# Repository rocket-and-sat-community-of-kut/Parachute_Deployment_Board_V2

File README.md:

# Parachute_Deployment_Board_V2

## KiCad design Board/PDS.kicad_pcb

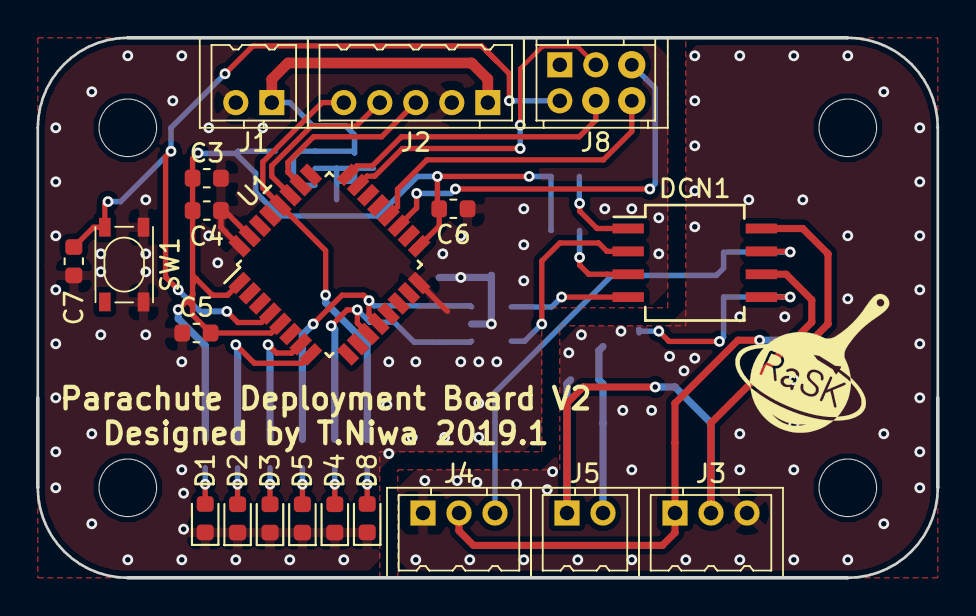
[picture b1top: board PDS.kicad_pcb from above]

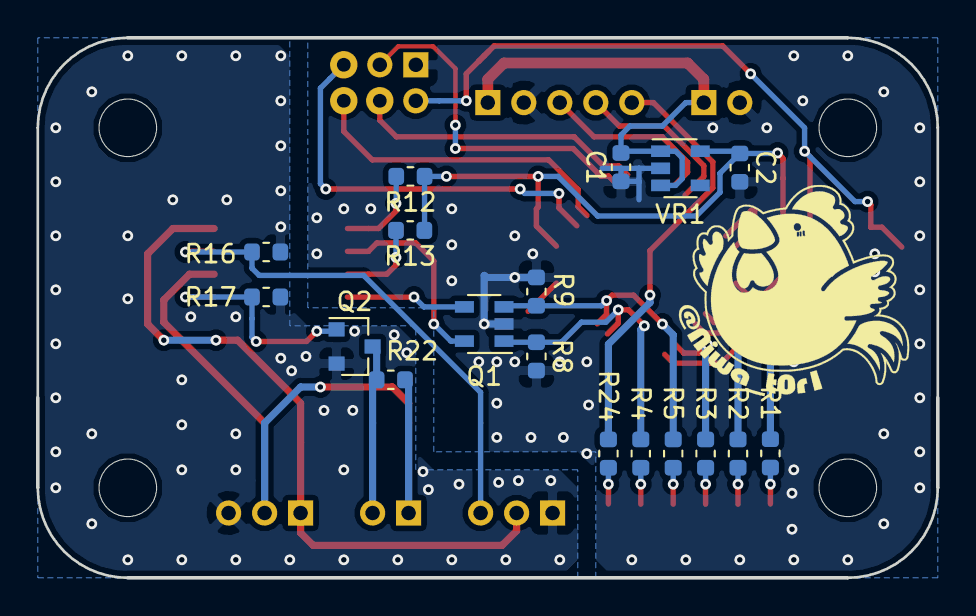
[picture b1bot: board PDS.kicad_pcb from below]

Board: 2 copper layers, 50.0 x 30.0 mm, 38 parts (18 on the bottom side), 31 nets.

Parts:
C1: 0.47u; C_0603_1608Metric
C2, C3: 4.7u; C_0603_1608Metric
C4, C6, C7: 0.1u; C_0603_1608Metric
C5: 0.01u; C_0603_1608Metric
D1, D2, D3, D8: LED; LED_0603_1608Metric
D4, D5: RED; LED_0603_1608Metric
DCN1: ACPL-227; SO-8_5.3x6.2mm_P1.27mm
J1: PWR; DF3A-2P-2DSA
J2: Port; DF3A-5P-2DSA
J3: Actuator_Port; DF3A-3P-2DSA
J4: Servo1; DF3A-3P-2DSA
J5: Air1; DF3A-2P-2DSA
J8: STLink+; DF11-6DP-2DSA2
Q1: DUAL; SOT-23-5
Q2: Q_NMOS_GSD; SOT-23
R1, R2, R3, R4, R5, R8, R9, R12, R13, R16, R17, R22, R24: 1k; R_0603_1608Metric
SW1: SW_Push_Dual; SW_SPST_SKRPACE010
U1: STM32F042K6Tx; LQFP-32_7x7mm_P0.8mm
VR1: NJM12888; SOT-23-5

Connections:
+3V3: C2.1, C3.2, C4.2, C5.2, C6.2, R1.1, R12.1, R13.1, U1.1, U1.5, U1.17, VR1.5
+6V: C1.1, J1.1, J2.1, VR1.1, VR1.3
/LED1: R2.1, U1.8
/LED2: R3.1, U1.7
/RESET: C7.1, J8.2, SW1.2, U1.4
AirGND1: J5.2, Q2.3, R22.1
AirVCC1: DCN1.6, J3.2, J5.1, R22.2
Debug_RX: J8.6, U1.20
Debug_TX: J8.5, U1.19
FPIN: J2.5, R24.1, U1.28
GND: C1.2, C2.2, C3.1, C4.1, C5.1, C6.1, C7.2, D1.1, D2.1, D3.1, D4.1, D5.1, D8.1, J1.2, J2.2, J8.1, Q1.2, R8.2, R9.2, SW1.3, SW1.4, U1.16, U1.31, U1.32, VR1.2
GNDPWR: J3.3, J4.1, Q2.2, R16.2, R17.2
unnamed: D1.2, R1.2
unnamed: D2.2, R2.2
unnamed: D3.2, R3.2
unnamed: D4.2, R4.2
unnamed: D5.2, R5.2
unnamed: D8.2, R24.2
unnamed: DCN1.1, R12.2
unnamed: DCN1.2, Q1.5
unnamed: DCN1.3, R13.2
unnamed: DCN1.4, Q1.4
unnamed: DCN1.5, Q2.1, R17.1
SIG1: Q1.1, R4.1, R8.1, U1.11
SIG2: Q1.3, R5.1, R9.1, U1.12
SWCLK: J8.4, U1.24
SWDIO: J8.3, U1.23
Servo1: DCN1.7, J4.3, R16.1
TRIG: J2.3, U1.26
TRIG2: J2.4, U1.27
VCC: DCN1.8, J3.1, J4.2

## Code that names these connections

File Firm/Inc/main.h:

/* USER CODE BEGIN Header */
/**
  ******************************************************************************
  * @file           : main.h
  * @brief          : Header for main.c file.
  *                   This file contains the common defines of the application.
  ******************************************************************************
  ** This notice applies to any and all portions of this file
  * that are not between comment pairs USER CODE BEGIN and
  * USER CODE END. Other portions of this file, whether 
  * inserted by the user or by software development tools
  * are owned by their respective copyright owners.
  *
  * COPYRIGHT(c) 2019 STMicroelectronics
  *
  * Redistribution and use in source and binary forms, with or without modification,
  * are permitted provided that the following conditions are met:
  *   1. Redistributions of source code must retain the above copyright notice,
  *      this list of conditions and the following disclaimer.
  *   2. Redistributions in binary form must reproduce the above copyright notice,
  *      this list of conditions and the following disclaimer in the documentation
  *      and/or other materials provided with the distribution.
  *   3. Neither the name of STMicroelectronics nor the names of its contributors
  *      may be used to endorse or promote products derived from this software
  *      without specific prior written permission.
  *
  * THIS SOFTWARE IS PROVIDED BY THE COPYRIGHT HOLDERS AND CONTRIBUTORS "AS IS"
  * AND ANY EXPRESS OR IMPLIED WARRANTIES, INCLUDING, BUT NOT LIMITED TO, THE
  * IMPLIED WARRANTIES OF MERCHANTABILITY AND FITNESS FOR A PARTICULAR PURPOSE ARE
  * DISCLAIMED. IN NO EVENT SHALL THE COPYRIGHT HOLDER OR CONTRIBUTORS BE LIABLE
  * FOR ANY DIRECT, INDIRECT, INCIDENTAL, SPECIAL, EXEMPLARY, OR CONSEQUENTIAL
  * DAMAGES (INCLUDING, BUT NOT LIMITED TO, PROCUREMENT OF SUBSTITUTE GOODS OR
  * SERVICES; LOSS OF USE, DATA, OR PROFITS; OR BUSINESS INTERRUPTION) HOWEVER
  * CAUSED AND ON ANY THEORY OF LIABILITY, WHETHER IN CONTRACT, STRICT LIABILITY,
  * OR TORT (INCLUDING NEGLIGENCE OR OTHERWISE) ARISING IN ANY WAY OUT OF THE USE
  * OF THIS SOFTWARE, EVEN IF ADVISED OF THE POSSIBILITY OF SUCH DAMAGE.
  *
  ******************************************************************************
  */
/* USER CODE END Header */

/* Define to prevent recursive inclusion -------------------------------------*/
#ifndef __MAIN_H
#define __MAIN_H

#ifdef __cplusplus
extern "C" {
#endif

/* Includes ------------------------------------------------------------------*/
#include "stm32f0xx_hal.h"

/* Private includes ----------------------------------------------------------*/
/* USER CODE BEGIN Includes */
#include "rocket.h"
/* USER CODE END Includes */

/* Exported types ------------------------------------------------------------*/
/* USER CODE BEGIN ET */

/* USER CODE END ET */

/* Exported constants --------------------------------------------------------*/
/* USER CODE BEGIN EC */

/* USER CODE END EC */

/* Exported macro ------------------------------------------------------------*/
/* USER CODE BEGIN EM */

/* USER CODE END EM */

void HAL_TIM_MspPostInit(TIM_HandleTypeDef *htim);

/* Exported functions prototypes ---------------------------------------------*/
void Error_Handler(void);

/* USER CODE BEGIN EFP */

/* USER CODE END EFP */

/* Private defines -----------------------------------------------------------*/
#define LED1_Pin GPIO_PIN_1
#define LED1_GPIO_Port GPIOA
#define LED2_Pin GPIO_PIN_2
#define LED2_GPIO_Port GPIOA
#define SERVO_Pin GPIO_PIN_5
#define SERVO_GPIO_Port GPIOA
#define AIR_Pin GPIO_PIN_6
#define AIR_GPIO_Port GPIOA
#define DEBUG_TX_Pin GPIO_PIN_9
#define DEBUG_TX_GPIO_Port GPIOA
#define DEBUG_RX_Pin GPIO_PIN_10
#define DEBUG_RX_GPIO_Port GPIOA
#define TRIG1_Pin GPIO_PIN_3
#define TRIG1_GPIO_Port GPIOB
#define TRIG1_EXTI_IRQn EXTI2_3_IRQn
#define TRIG2_Pin GPIO_PIN_4
#define TRIG2_GPIO_Port GPIOB
#define TRIG2_EXTI_IRQn EXTI4_15_IRQn
#define FPIN_Pin GPIO_PIN_5
#define FPIN_GPIO_Port GPIOB
#define FPIN_EXTI_IRQn EXTI4_15_IRQn
/* USER CODE BEGIN Private defines */

/* USER CODE END Private defines */

#ifdef __cplusplus
}
#endif

#endif /* __MAIN_H */

/************************ (C) COPYRIGHT STMicroelectronics *****END OF FILE****/
